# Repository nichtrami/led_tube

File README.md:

# LED Tube

## Overview
This project controls **2-meter-long LED tubes** built from a **WS2812B LED strip with 120 LEDs**.
The firmware runs on an **ESP32 (Arduino Core)** and supports standalone operation, a custom
**wireless DMX protocol over ESP-NOW**, wired **DMX input**, and an (experimental) **Art-Net** path.

The codebase builds two different devices from the same sources, selected via the `DEVICE_MODE`
build flag in [`platformio.ini`](platformio.ini):

| Device | PlatformIO env | Board | Role |
| ------ | -------------- | ----- | ---- |
| **Tube**   | `led_tube` | Seeed XIAO ESP32-S3 | Drives one LED tube and receives commands |
| **Bridge** | `bridge`   | ESP32 dev board     | Generates/forwards commands to the tubes  |

## Hardware Components
Schematics and PCB designs live in `pcb/`, enclosure models in `body/`.

Datasheets for the components used are not redistributed in this repository. The part numbers are
given in the schematics and can be looked up on the manufacturers' sites.

### User Interface (both devices)
- **Three buttons**: Up, Down, Enter
- **A monochrome 0.91" OLED display** (SSD1306) connected via **I2C**, showing the current menu item

## Operating Modes

### Tube
1. **Standalone** – the tube shows a locally selected color and effect.
2. **Wireless DMX** – the tube listens on a configurable DMX address and renders the data it
   receives from a bridge over ESP-NOW.

### Bridge
1. **Master** – generates beat-synchronized choreography (driven by a configurable BPM) for a
   configurable number of tubes and broadcasts it over ESP-NOW.
2. **DMX** – reads a wired DMX universe (via `esp_dmx`) and forwards the relevant slice to the
   tubes over ESP-NOW.
3. **Art-Net** – receives Art-Net over Ethernet (W5500). *Experimental / partially implemented.*

### Channels
The **Channel** menu item (1–3) maps to distinct Wi-Fi channels for the ESP-NOW link, so multiple
independent light systems can run side by side without interference. The bridge and its tubes must
use the same channel.

## Wireless Protocol
Communication uses **ESP-NOW broadcast** (no pairing). The payload is a lightweight DMX frame:

```
[ size (1 byte) ][ start_address (1 byte) ][ data ... up to 240 bytes ]
```

Each tube occupies `TUBE_DATASET_SIZE` (4) channels: `effect, red, green, blue`.

## Pin Configuration
Pins are defined in [`src/Config.hpp`](src/Config.hpp).

### Tube (Seeed XIAO ESP32-S3)
- **LED data**: GPIO 4
- **OLED (I2C)**: SDA GPIO 3, SCL GPIO 2
- **Buttons**: Up GPIO 9, Down GPIO 7, Enter GPIO 8

### Bridge (ESP32 dev board)
- **LED data**: GPIO 14
- **OLED (I2C)**: SDA GPIO 26, SCL GPIO 25
- **Buttons**: Up GPIO 27, Down GPIO 32, Enter GPIO 33
- **DMX input**: RX GPIO 16, EN/TX GPIO 17
- **Ethernet (W5500, SPI)**: CS GPIO 5, SCK GPIO 18, MISO GPIO 19, MOSI GPIO 23, RST GPIO 4

## Building & Flashing
This is a [PlatformIO](https://platformio.org/) project.

```bash
# Tube firmware
pio run -e led_tube -t upload

# Bridge firmware
pio run -e bridge -t upload
```

Configuration values selected in the on-device menu are persisted to NVS flash and restored on boot.

### Dependencies
Managed automatically by PlatformIO (see [`platformio.ini`](platformio.ini)):
- FastLED
- Adafruit GFX Library
- Adafruit SSD1306
- esp_dmx
- Ethernet
- ArtNet

ESP-NOW / Wi-Fi and `Preferences` (NVS) are provided by the ESP32 Arduino Core.

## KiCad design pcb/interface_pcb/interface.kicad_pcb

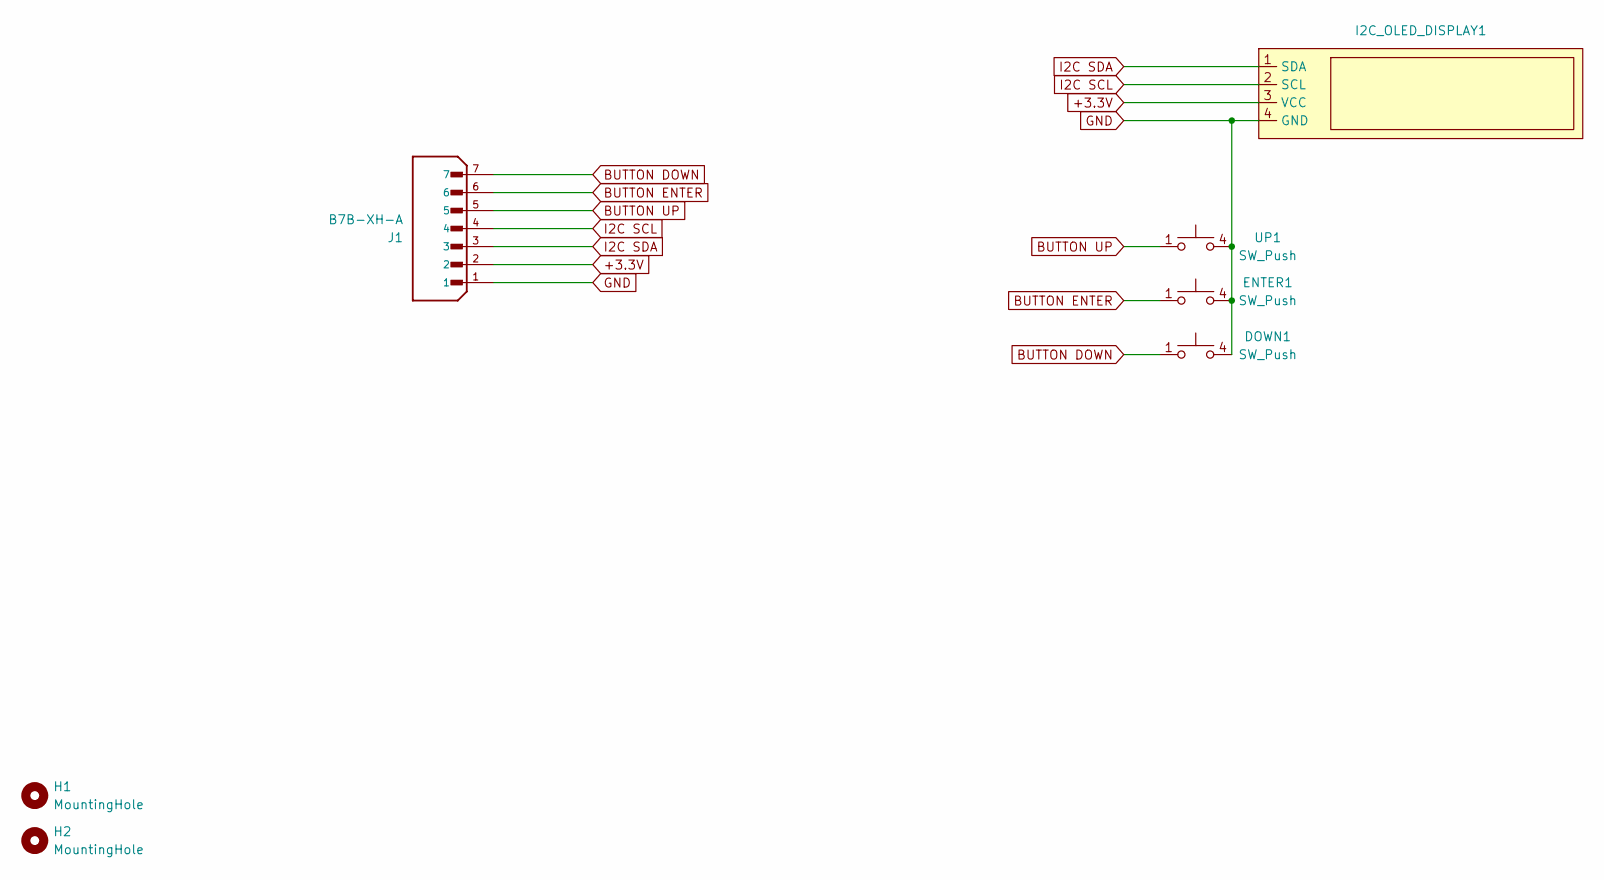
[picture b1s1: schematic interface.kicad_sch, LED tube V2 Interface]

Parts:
DOWN1: SW_Push; SW_1825910-6-4
ENTER1: SW_Push; SW_1825910-6-4
H1, H2: MountingHole; MountingHole_2.2mm_M2
I2C_OLED_DISPLAY1: MODULE_DM-OLED096-636
J1: B7B-XH-A; JST_B7B-XH-A; PARTREV 7/4/21
UP1: SW_Push; SW_1825910-6-4

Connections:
+3.3V: I2C_OLED_DISPLAY1.3 (VCC), J1.2
BUTTON DOWN: DOWN1.1, J1.7
BUTTON ENTER: ENTER1.1, J1.6
BUTTON UP: J1.5, UP1.1
GND: DOWN1.4, ENTER1.4, I2C_OLED_DISPLAY1.4 (GND), J1.1, UP1.4
I2C SCL: I2C_OLED_DISPLAY1.2 (SCL), J1.4
I2C SDA: I2C_OLED_DISPLAY1.1 (SDA), J1.3

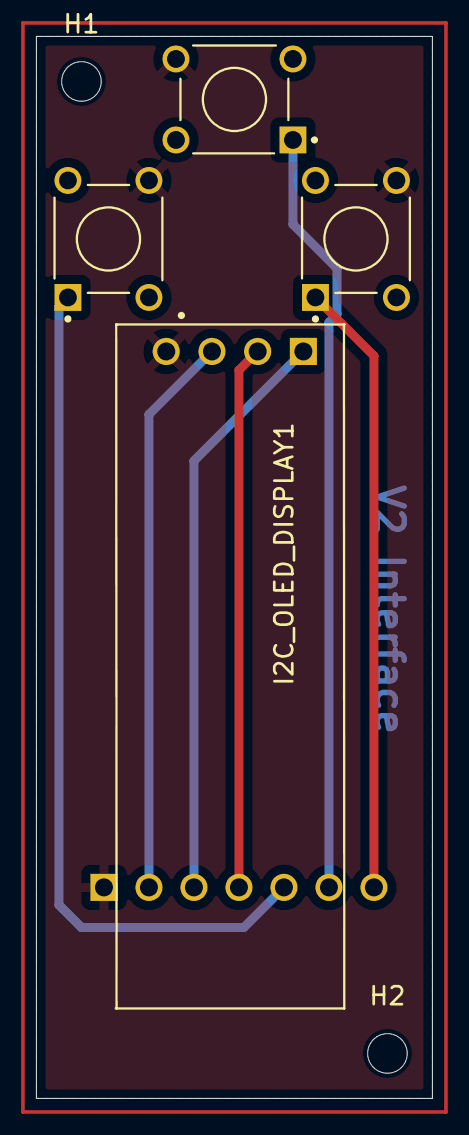
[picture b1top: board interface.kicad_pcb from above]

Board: 2 copper layers, 22.0 x 59.0 mm, 7 parts (1 on the bottom side), 7 nets.

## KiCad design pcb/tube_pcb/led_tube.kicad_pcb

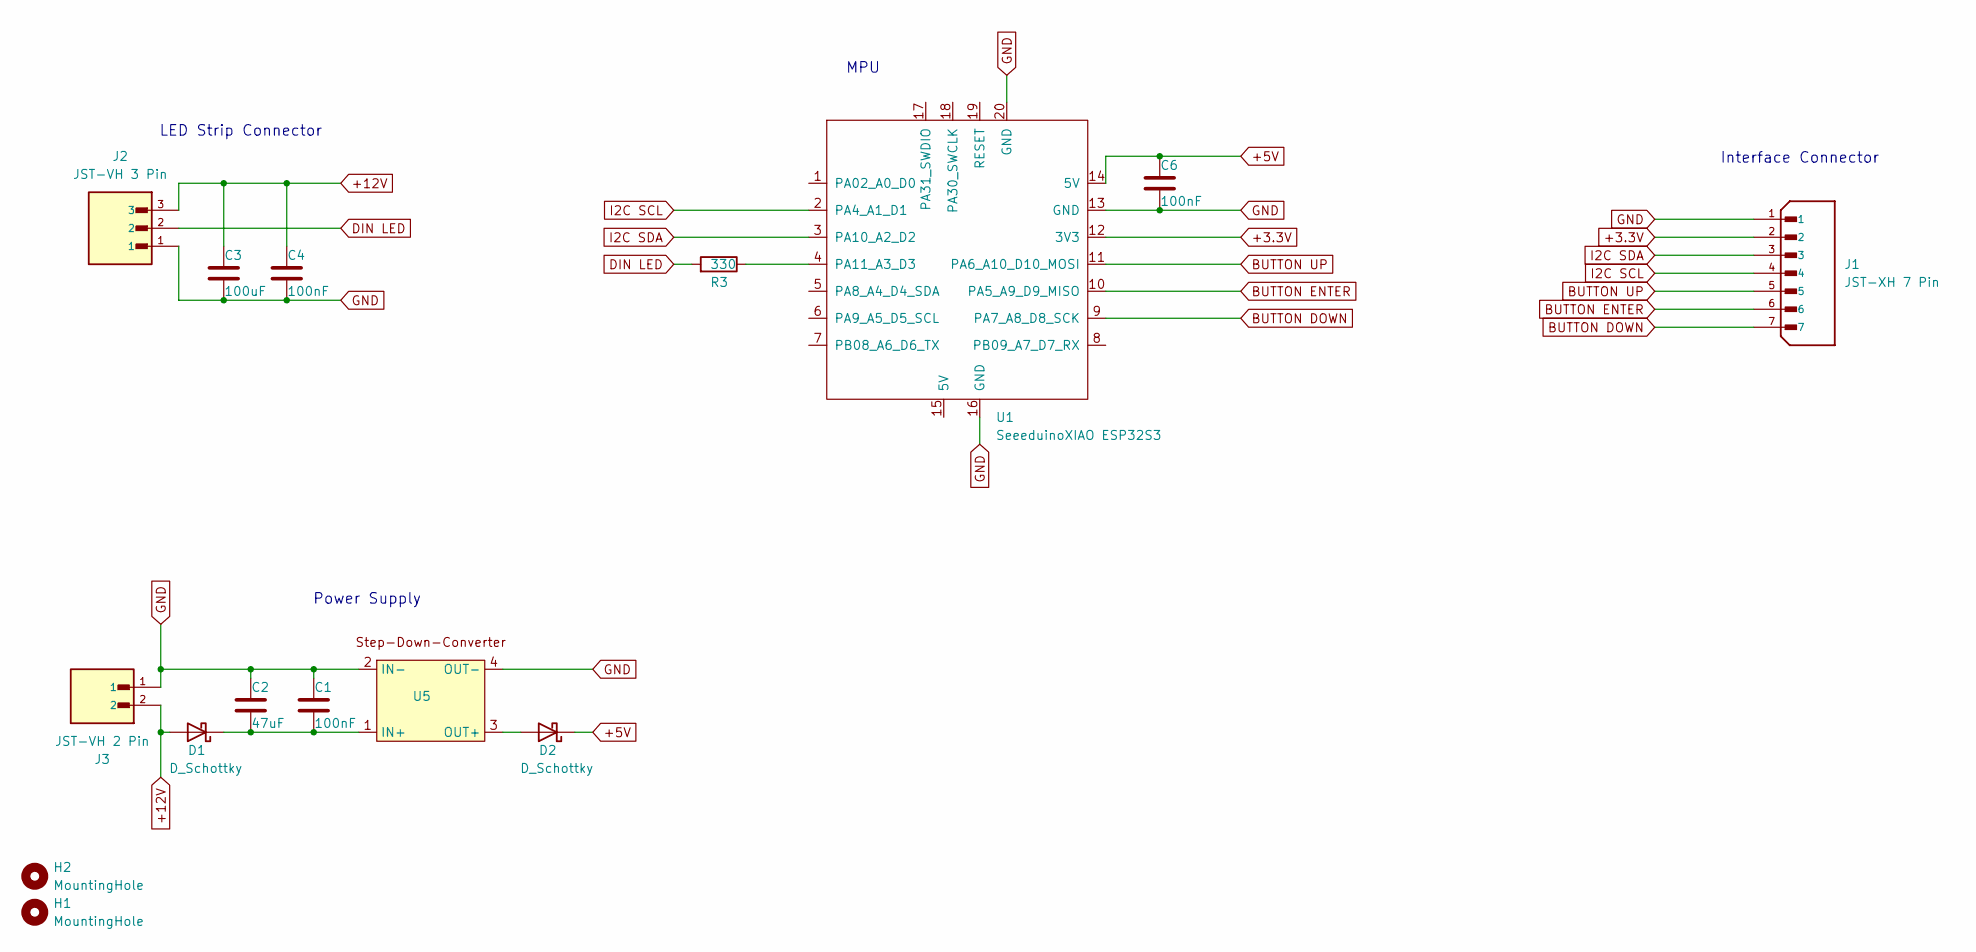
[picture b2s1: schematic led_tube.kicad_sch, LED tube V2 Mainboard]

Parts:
C1, C4, C6: 100nF; C_1206_3216Metric
C2: 47uF; C_1206_3216Metric
C3: 100uF; C_1206_3216Metric
D1, D2: D_Schottky; D_SMA_Handsoldering
H1, H2: MountingHole; MountingHole_2.2mm_M2
J1: JST-XH 7 Pin; JST_B7B-XH-A; PARTREV 7/4/21
J2: JST-VH 3 Pin; JST_B3P-VH_LF__SN_; PARTREV NA
J3: JST-VH 2 Pin; JST_B2P-VH_LF__SN_; PARTREV NA
R3: 330; R_1206_3216Metric
U1: SeeeduinoXIAO ESP32S3; Seeeduino XIAO-MOUDLE14P-2.54-21X17.8MM
U5: Step-Down-Converter DCDC

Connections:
+3.3V: J1.2, U1.12 (3V3)
+5V: C6.1, D2.1 (K), U1.14 (5V)
+12V: C3.1, C4.1, D1.2 (A), J2.3, J3.2
BUTTON DOWN: J1.7, U1.9 (PA7_A8_D8_SCK)
BUTTON ENTER: J1.6, U1.10 (PA5_A9_D9_MISO)
BUTTON UP: J1.5, U1.11 (PA6_A10_D10_MOSI)
DIN LED: J2.2, R3.2
GND: C1.1, C2.1, C3.2, C4.2, C6.2, J1.1, J2.1, J3.1, U1.13 (GND), U1.16 (GND), U1.20 (GND), U5.2 (IN-), U5.4 (OUT-)
I2C SCL: J1.4, U1.2 (PA4_A1_D1)
I2C SDA: J1.3, U1.3 (PA10_A2_D2)
unnamed: C1.2, C2.2, D1.1 (K), U5.1 (IN+)
unnamed: D2.2 (A), U5.3 (OUT+)
unnamed: R3.1, U1.4 (PA11_A3_D3)

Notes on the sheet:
Power Supply
LED Strip Connector
Interface Connector
MPU

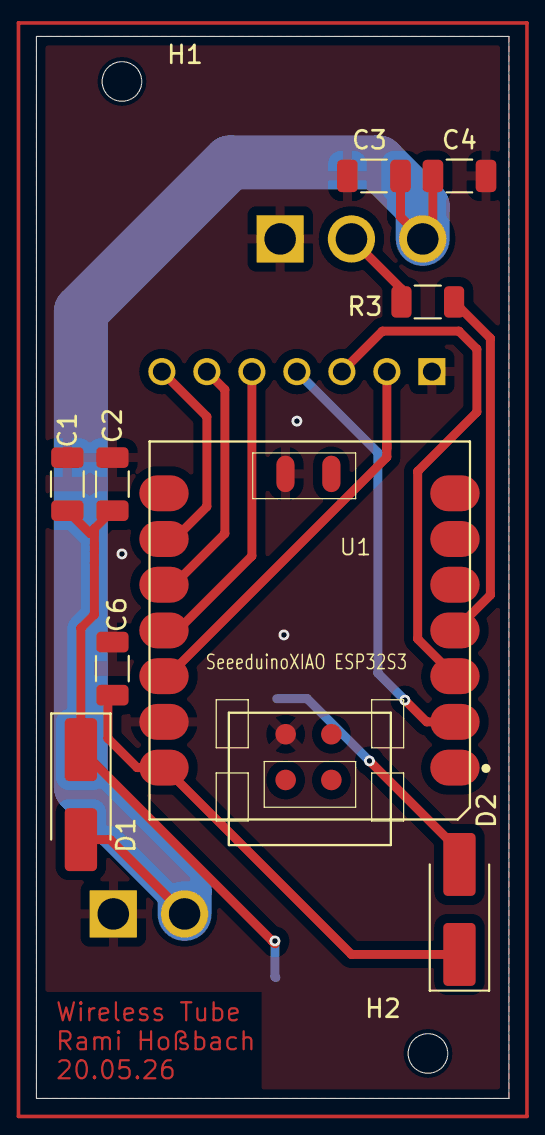
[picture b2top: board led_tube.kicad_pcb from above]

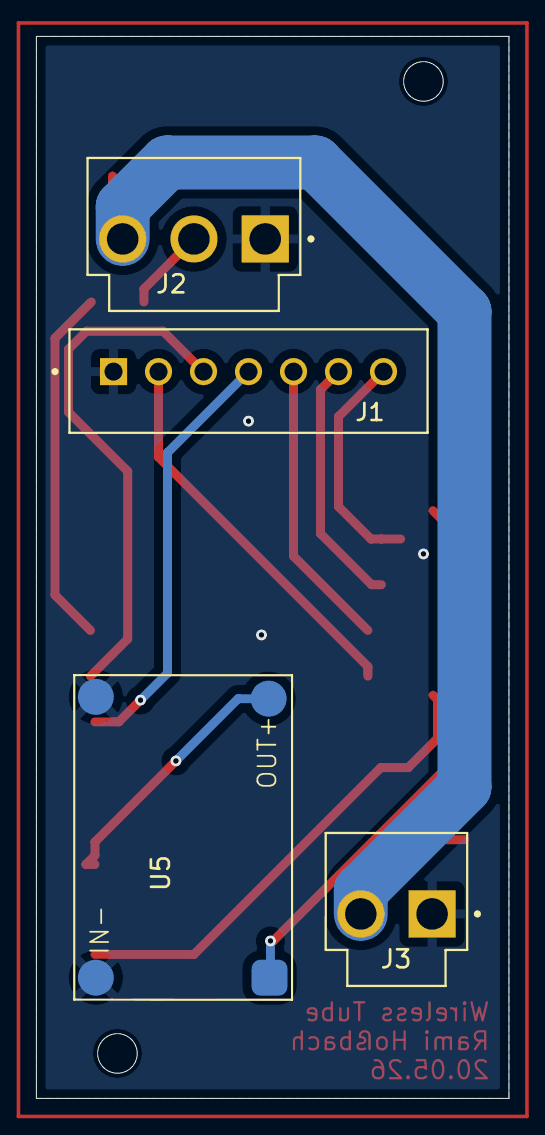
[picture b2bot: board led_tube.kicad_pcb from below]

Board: 2 copper layers, 26.2 x 59.0 mm, 15 parts (4 on the bottom side), 13 nets.

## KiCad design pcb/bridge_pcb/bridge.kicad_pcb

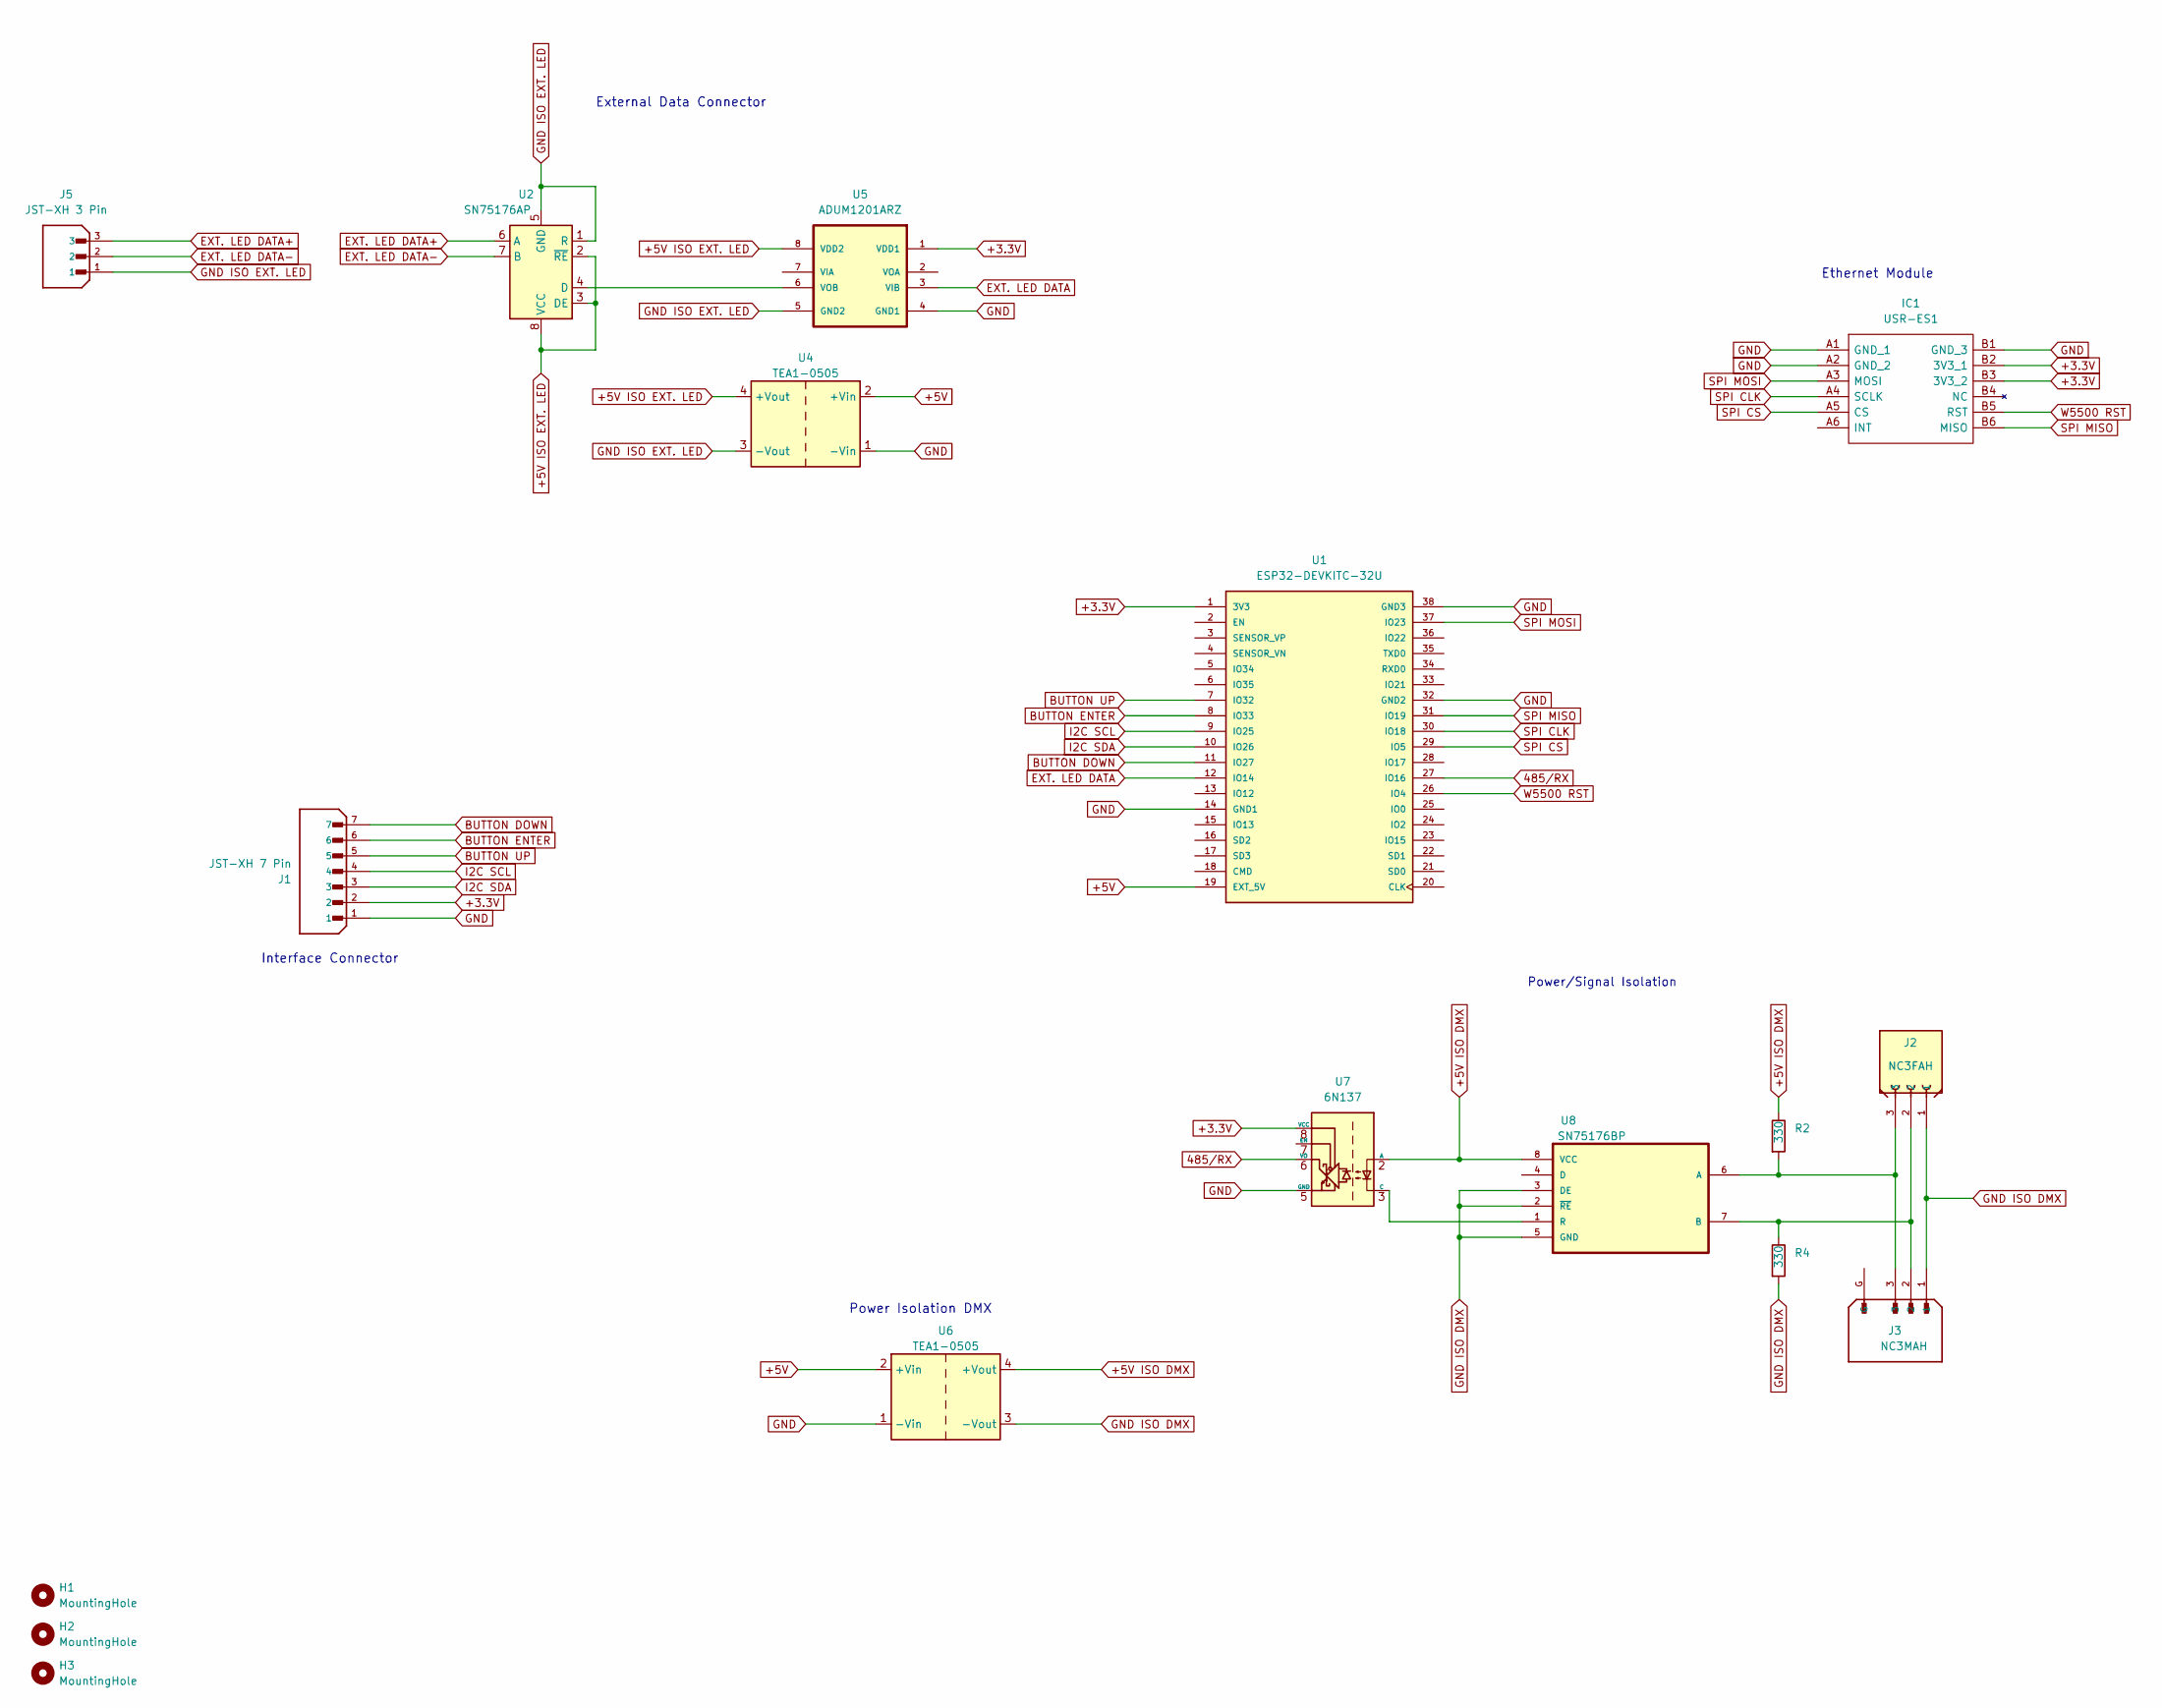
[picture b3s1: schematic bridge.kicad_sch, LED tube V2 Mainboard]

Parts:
H1, H2, H3: MountingHole; MountingHole_3.2mm_M3
IC1: USR-ES1; USRES1; Manufacturer_Part_Number USR-ES1
J1: JST-XH 7 Pin; JST_B7B-XH-A; PARTREV 7/4/21
J2: NC3FAH; NEUTRIK_NC3FAH; PARTREV 07.03.19
J3: NC3MAH; NEUTRIK_NC3MAH; PARTREV 30.03.09
J5: JST-XH 3 Pin; JST_XH-A_LF__SN_3-Pin; PARTREV 7/4/21
R2, R4: 330; R_1206_3216Metric
U1: ESP32-DEVKITC-32U; MODULE_ESP32-DEVKITC-32U; PARTREV V4
U2: SN75176AP; DIP-8_W7.62mm
U4, U6: TEA1-0505; Converter_DCDC_TRACO_TEA1-xxxx_THT
U5: ADUM1201ARZ; MPN ADUM1201ARZ
U7: 6N137; DIP-8_W7.62mm
U8: SN75176BP; DIP794W45P254L959H508Q8

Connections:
485/RX: U1.27 (IO16), U7.6 (VO)
+3.3V: IC1.B2 (3V3_1), IC1.B3 (3V3_2), J1.2, U1.1 (3V3), U5.1 (VDD1), U7.8 (VCC)
+5V: U1.19 (EXT_5V), U4.2 (+Vin), U6.2 (+Vin)
+5V ISO DMX: R2.1, U6.4 (+Vout), U7.2 (A), U8.8 (VCC)
+5V ISO EXT. LED: U2.2 (~RE), U2.3 (DE), U2.8 (VCC), U4.4 (+Vout), U5.8 (VDD2)
BUTTON DOWN: J1.7, U1.11 (IO27)
BUTTON ENTER: J1.6, U1.8 (IO33)
BUTTON UP: J1.5, U1.7 (IO32)
EXT. LED DATA: U1.12 (IO14), U5.3 (VIB)
EXT. LED DATA+: J5.3, U2.6 (A)
EXT. LED DATA-: J5.2, U2.7 (B)
GND: IC1.A1 (GND_1), IC1.A2 (GND_2), IC1.B1 (GND_3), J1.1, U1.14 (GND1), U1.32 (GND2), U1.38 (GND3), U4.1 (-Vin), U5.4 (GND1), U6.1 (-Vin), U7.5 (GND)
GND ISO DMX: J2.1, J3.1, R4.2, U6.3 (-Vout), U8.2 (~RE), U8.3 (DE), U8.5 (GND)
GND ISO EXT. LED: J5.1, U2.1 (R), U2.5 (GND), U4.3 (-Vout), U5.5 (GND2)
I2C SCL: J1.4, U1.9 (IO25)
I2C SDA: J1.3, U1.10 (IO26)
unnamed: U2.4 (D), U5.6 (VOB)
unnamed: U7.3 (C), U8.1 (R)
unnamed: J2.3, J3.3, R2.2, U8.6 (A)
unnamed: J2.2, J3.2, R4.1, U8.7 (B)
SPI CLK: IC1.A4 (SCLK), U1.30 (IO18)
SPI CS: IC1.A5 (CS), U1.29 (IO5)
SPI MISO: IC1.B6 (MISO), U1.31 (IO19)
SPI MOSI: IC1.A3 (MOSI), U1.37 (IO23)
W5500 RST: IC1.B5 (RST), U1.26 (IO4)

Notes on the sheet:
External Data Connector
Power/Signal Isolation
Power Isolation DMX
Interface Connector
Ethernet Module

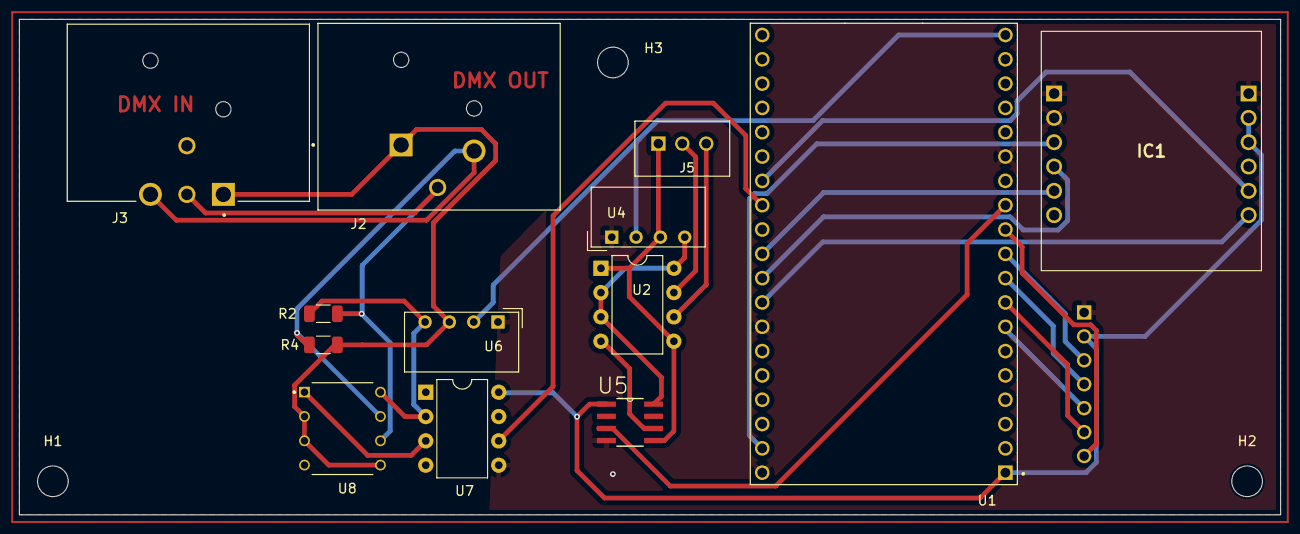
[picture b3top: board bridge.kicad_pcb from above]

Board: 2 copper layers, 131.8 x 51.8 mm, 17 parts (1 on the bottom side), 25 nets.
